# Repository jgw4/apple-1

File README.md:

This repository is a collection of different projects I've found around the internet relating to building a near-exact clone of the Apple-1 computer, as well as the home of the "Doppel-1" replica Apple-1 PCB. My intention is for it to act as a central repository for information that may otherwise be obscure decentralized, or link rot in the future. For aspiring builders, having everything in one place helps with prep work, troubleshooting, and familiarizes with the scope of the project.

For more information on each project, see the README.md within each subdirectory listed below.

## Contents
For further information on the projects in questions, read the README.md within each directory:

[`/mainboard/`](./mainboard/) - Project folder for the Doppel-1

[`/doc/`](./doc/) - Contains various instruction manuals for building, soldering, wiring, and using the Apple-1 and its various accessories

[`/aci/`](./aci/) - Project folder for rebuilding the Apple Cassette Interface in KiCad (Complete)

[`/serialboard/`](./serialboard/) - Project folder for rebuilding the Apple Serial Interface in KiCad

[`/graphicard/`](./graphicard/) - Mirror and minor alteration of the original P-L4B graphics card [here](https://p-l4b.github.io/graphic/) based on the Texas Instruments VDP TMS9918A. It has been modified cosmetically to look more similar to the Apple Cassette Interface. This project is licensed under CC BY 4.0 by the creator.

[`/protoboard/`](./protoboard/) - Mirror and minor alteration of the original P-L4B proto board [here](https://p-l4b.github.io/proto/). It has been modified cosmetically to look more similar to the Apple Cassette Interface. This project is licensed under CC BY 4.0 by the creator.

[`/risercard/`](./risercard/) - Mirror and minor alteration of the original P-L4B riser board [here](https://p-l4b.github.io/riser/). It has been modified cosmetically to look more similar to the Apple Cassette Interface. This project is licensed under CC BY 4.0 by the creator.

[`/datanetics_modern/`](./datanetics_modern/)- Datanetics Keyboard - Modern Version (Built by [@schlae](https://github.com/schlae/replica-datanetics))

[`/datanetics_original`](./datanetics_original/) - Datanetics Keyboard (Original) (Built by [willegal](https://www.willegal.net/appleii/apple1-datanetics.htm))

[`/software/`](./software/) - A repository of Cassette interface software (.wav) files for use with the Apple-1

[`/fw/`](./fw/) - Copies of wozmon.asm and wozaci.asm firmware files

[`/img/`](./img/) - support image files for various projects

## Other Things to check out

[P-Lab Projects](https://p-l4b.github.io) - Hosts various neat expansion cards and mods for the apple-1, such as a Wi-Fi Card, SD Storage card, riser card, sound card, Video card, various IC replacement boards, expansion port breadboards, and much more. Really cool stuff!

[Erik's Ponderings - Building an Apple-1](https://blog.bruchez.name/posts/apple-1-reproduction-part-1-components/) - Erik Bruchez documented his process of building an exceptional Apple-1 clone in great detail, including some great tips for power supply building, adding more decoupling capacitors, mechanical tips, and more. Really neat to check out, especially before you build one of your own

## Goals and Contributing

If you'd like to contribute, I'm always happy to accept work on anything that makes these files more accurate and complete. For more details, see the `readme.md` file located within each board's folder

### Schematics
- Schematic files need creating for the original Datanetics keyboard
### Gerber Files
Gerbers based on the PCB files have not yet been generated. only the original imported gerbers are located within the respective board's folder

## Future Goals
In the future, once the above goals are met and I'm satisfied with them, I may consider working on an altered version of the main board that, while maintaining the same number and nature of the components, makes adequate substitutes such that another curious hobbyist would be able to buy as many components as possible off-the-shelf without having to hunt for "unicorn" parts. I'd also like to address electrical issues found by various hobbyists relating to stability and performance of the board

I'd like the ability to build one to be cheap and available to anyone who wants to do it, without having to sacrifice much at all in the way of board or schematic integrity. I would also like to provide a BOM that includes all required sockets needed for all the DIP chips in the system

## Acknowledgements

This repository contains only a fraction of original work. mostly, it is an amalgamation of a few different projects related to documenting and reproducing the Apple-1 Computer, with my work being mainly relegated to tying the gerber files and schematics together into a cohesive whole KiCad project. The attributions for the various portions of the project files are in the table above
* I am not sure the original source of the Mainboard PCB gerber files. the Applefritter forum post remarks that they were posted on an Apple-1 enthusiasts facebook group, but I do not have facebook nor would i know how to track down the original post. If anyone can give proper attribution to the files please reach out.

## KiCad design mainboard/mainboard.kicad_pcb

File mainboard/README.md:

# About the "Doppel-1"
My personal contributions to this repo is the "Doppel-1", a new Replica PCB that is somewhat unique among clone boards floating around the internet. This is being done by working off of an imported copy of gerber files for the "PCB-11" replica that I found on [Applefritter Forums](https://www.applefritter.com/content/apple-1-replica-gerber-files), which were posted originally on a facebook group. The "PCB-11" is, I believe, the most common replica board you will see pictures of online as this is the only replica (that I know of) where the gerbers have been made publicly available. These are often marked on the back in the bottom right with "Apple 1 replica 2012-2016" in soldermasked copper. If a replica board was purchased post-2020, it is likely that it is based on these gerber files, as the Mimeo-1 has been out of production since that time and up unto the time of writing.

The Doppel-1 can be considered a complete native rebuilding of "PCB-11" in KiCad, whereby the board has its own set of custom footprints that are unique to the apple-1, 3d models, native KiCad filled zones, rule areas, text elements (where possible), traces, and netclasses, as well as error fixes and fabrication notes for a production-ready PCB. Notable mistakes from the original vary from the file itself, to the schematics, to fabrication choices by the customer or the manufacturer. Clarifying remarks have been made to ensure that the PCB is being fabricated to make a reasonable replica. 

## Status of the Doppel-1

* All footprints have been designed, linked, and placed on the board
* All board text is contained within the top board layer. I have decided that there is no font matched well enough at this time to rely on a font alone. Only shapes have been redrawn at the footprint level.
* Need to fix issues with a few improper diode silkscreen arrow placements
* Proper trace widths and clearances still need assigned to all traces, ensuring proper spacing from all solder pads and enforcing a more rigorous Design Rules Check.
* a few remaining schematic parity errors.

## Design Notes And Changes
I have made some remarks about my observations so far:

1) The silkscreen text on the Apple-1 PCB is extremely difficult to reproduce. By all accounts it was hand-stenciled, and I have spent more time than I care to admit comparing uniform-stroke technical typefaces that are meant to replicate leroy lettering or other technical stencil packages that are freely available online, but none of them have quite matched what I have seen on the PCB-11 and on other clones. I have messed around with the font "Routed Gothic" and found it to be closest but kerning is not quite there, and it still does not match with the characters aforementioned. I can hack my way to passable kerning by adjusting the height-width ratio of the text boxes but it is not ideal. I believe Iwater GMaru Gothic Pro is a better match to the original, however that is a paid font that I am unwilling to obtain due to licensing. For any future work on a custom font for this computer, I have included a character "Proof Area" in the PCB file which contains every character on the board.

2) The solder pads on the DIP sockets and breadboard area on "PCB-11" are round on both front and back layers, while on original units, the solderpads were actually different on the back side vs the front. On the back they were a squashed oval (basically an obround but the end arcs share a center point with the rectangle's center point), and on the front they were smaller, tangent obrounds. This was most likely done to make it easy to solder while leaving room for trace paths on the front. This is something a lot of replicas miss.

3) The trace leading to the positive lead between B&C @16 has been adjusted to match the Mimeo-1

4) The trace between C&D @15 leeting to the via below IN914 diode at a 45 degree angle has been moved down slightly to match the Mimeo-1

5) silkscreen outlines for DIP sockets has been increased to a width of 10mils to match what is expected

6) In the original manual's schematics, as well as the ones made by Nicolas, there is an error in the pinouts listed for the TO-220 diodes (REG1,REG3,REG4/LM320 MP-5/LM320 MP-12/LM340 MP-12). LM320 has ground at pin 1, while in and out are pins 2&3, respectively.LM340 has ground at 2 and in/out at 1/3 like a more standard diode in this package. This was discovered by DRC error checking.

7) The top right mounting via has been moved right 100mils to match Mike Willegal's case dimension [here](https://www.willegal.net/appleii/apple1-enclosure.htm). My assumption is that these are truer than what were originally on the board

8) The original applefritter post had a user comment that noted the following issues. My comments are appended to the original marks:
- The original has a matte finish, this one has a sligtly brighter green - This is a fabrication preference/availability, not with the design of the board. see "Manufacturing Notes".
- The silkscreen doesn't cover the plated areas without soldermask.
- The DIP and breadboard solder pads should be wider although it only really matters in the breadboard area. - See point 2 above, much scrutiny went into the shape of the dip pads on this board.
- The video adjustment pot pads are  narrower by 0.025", making it difficult to insert the trimpot. - The 100 Ohm pot has been replaced with a standard footprint that should rectify the issue

## Manufacturing Notes:

If you are going to get your own replica board manufactured, read this first:

1) Normally the green finish provided by PCB manufacturers is way too dark. It has become clear to me that it will be almost impossible to replicate near-exact finishes for small volume with any direct-to-customer fabricators. If the fabricator does allow for lighter green finishes and/or matte green, these colors should be selected instead of a "Standard" green.

2) Boards that are finished with hard gold or using an ENIG process (i.e. full-board gold plating) are unable to also accomodate silkscreening on top of non-soldermasked copper. This is extremely evident in the top-right corner of the board where diode markings are missing where the gold is plated over the copper. It is understandable to desire gold for the longevity of the board, but doing so will produce a poor replica. Gold plating should be confined to the edge fingers only, with the rest done in HAL SnPb.

## Why?

Why did I do this? as Mike Willegal said, If you have to ask that question, this project isn't for you. I have had a strange fascination for the Apple-1 ever since I was a kid. I've been drawn to the technical artistry of the board, the simplicity of it, and find the assembly process and case design around it a very cool method of self-expression.

# Contributing
1) To properly view the pcb file's text elements, please download and install "Routed Gothic" font located in `/doc/`. This is the closest match I have found to the original PCB lettering in font form and is based on the Leroy stenciling system common with draftsman before computer fonts.

2) I have a near certain guess that the original apple-1 pcb was designed using mils. Thus, I would strongly encourage any user working on this board to set their units to mils and not mm. The original PCB-11 file was most likely not made by an American, as there are many metric dimensions scattered throughout the document. However building in nice round mil numbers should be the standard for this project

3) please submit a pull request listing in detail all changes you have made or would like to make, preferably with pictures. This can help avoid any duplicate work

4) Issues can also be raised, which I also enthusiastically accept. If you spot issues with the design of the board, please post an issue to the repository.

5) I am looking also for some more specific input on trace clearance. Since resizing the dip solderpads, clearance has been the biggest DRC issue. I would like to know what spacing was used on the original board so I can preserve that. Current clearance is set at 5 mils.

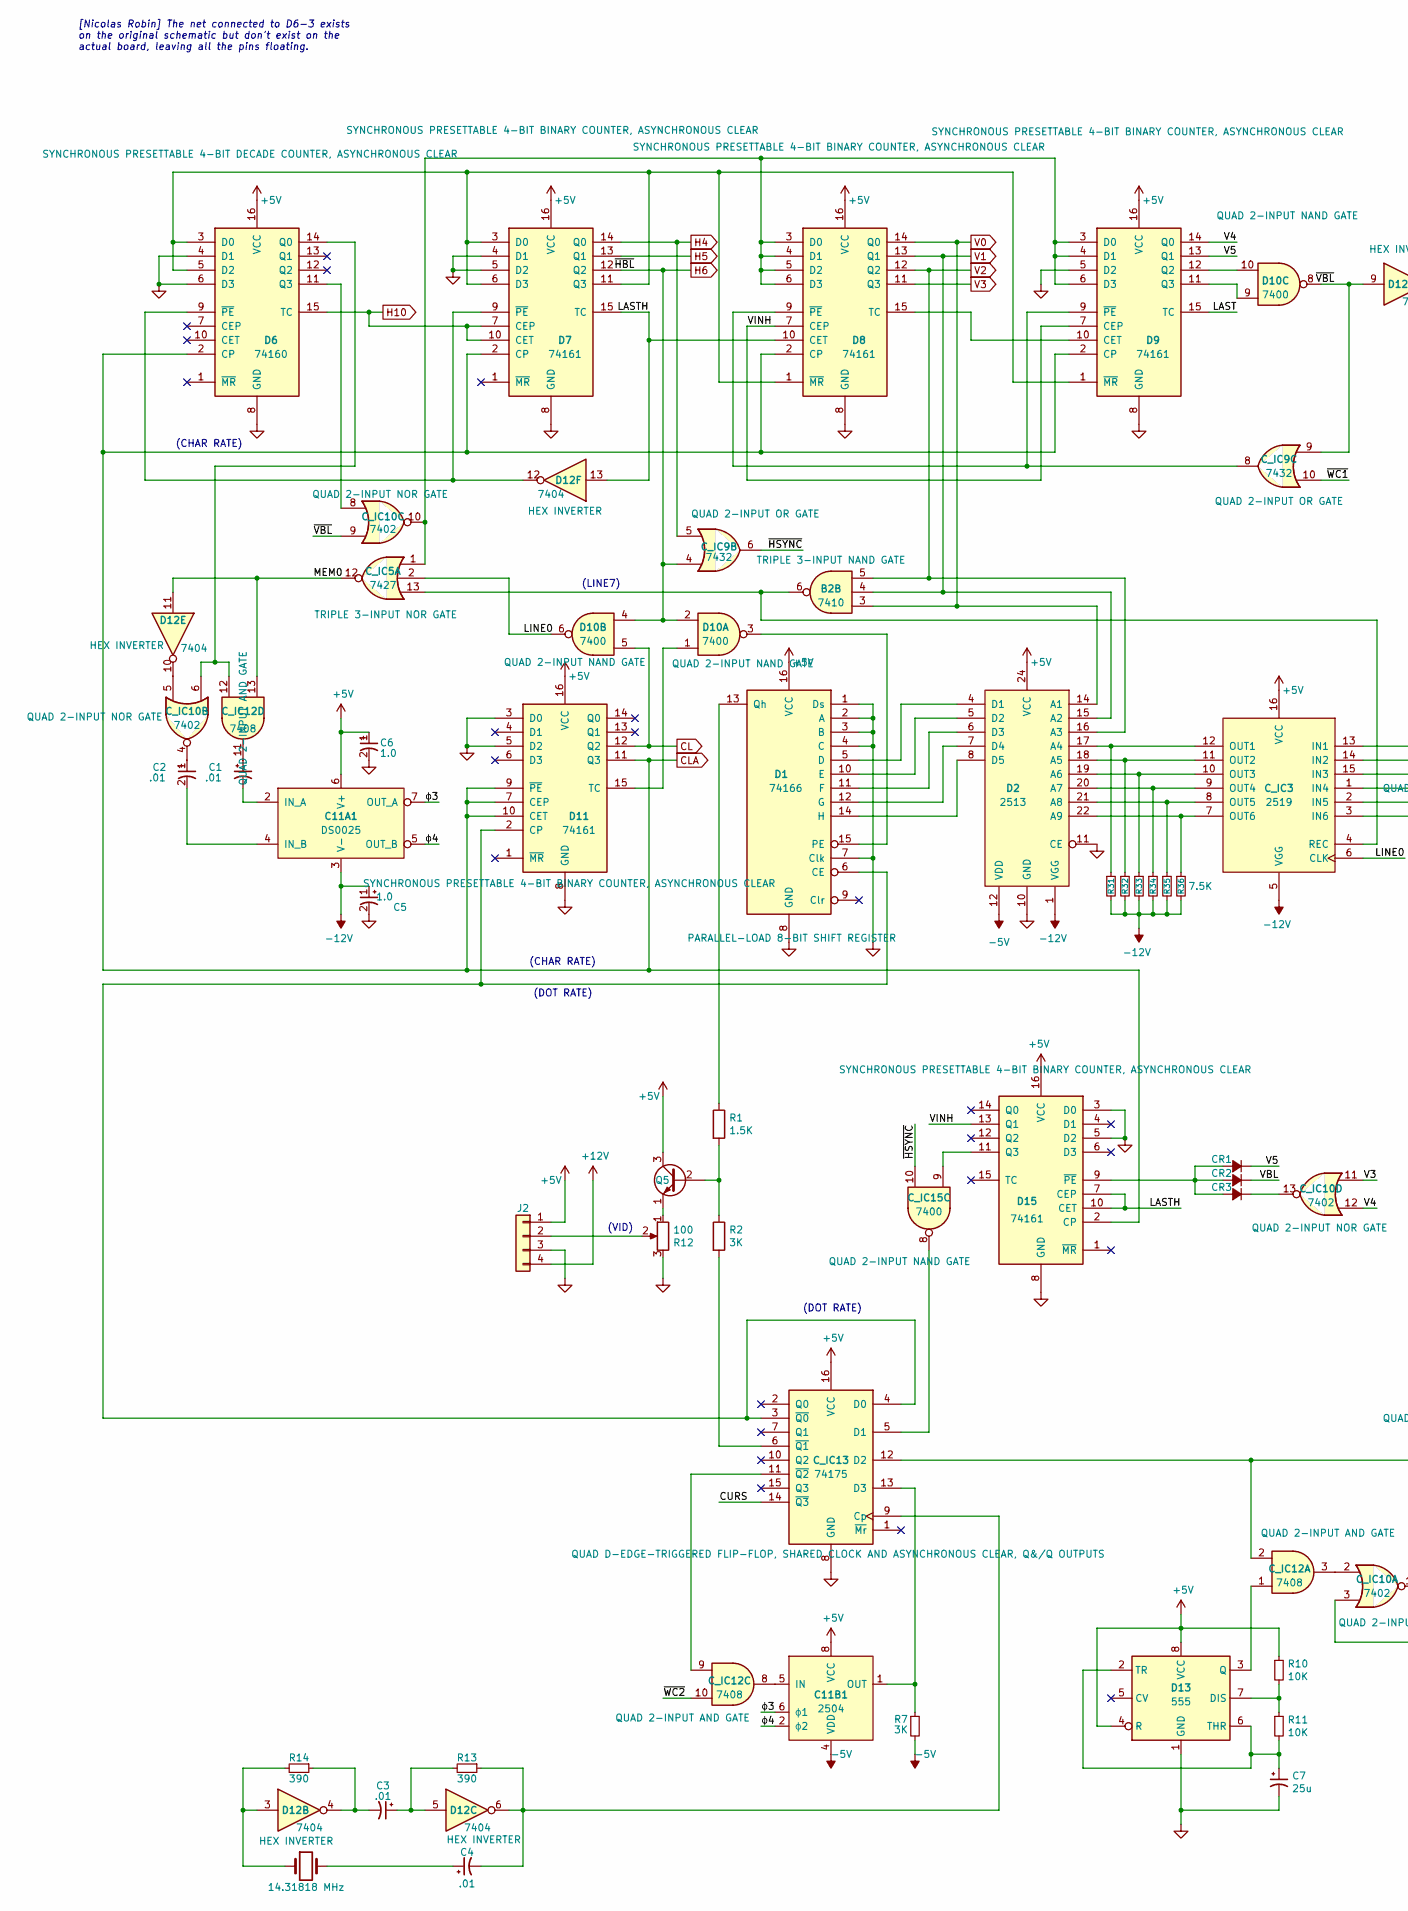
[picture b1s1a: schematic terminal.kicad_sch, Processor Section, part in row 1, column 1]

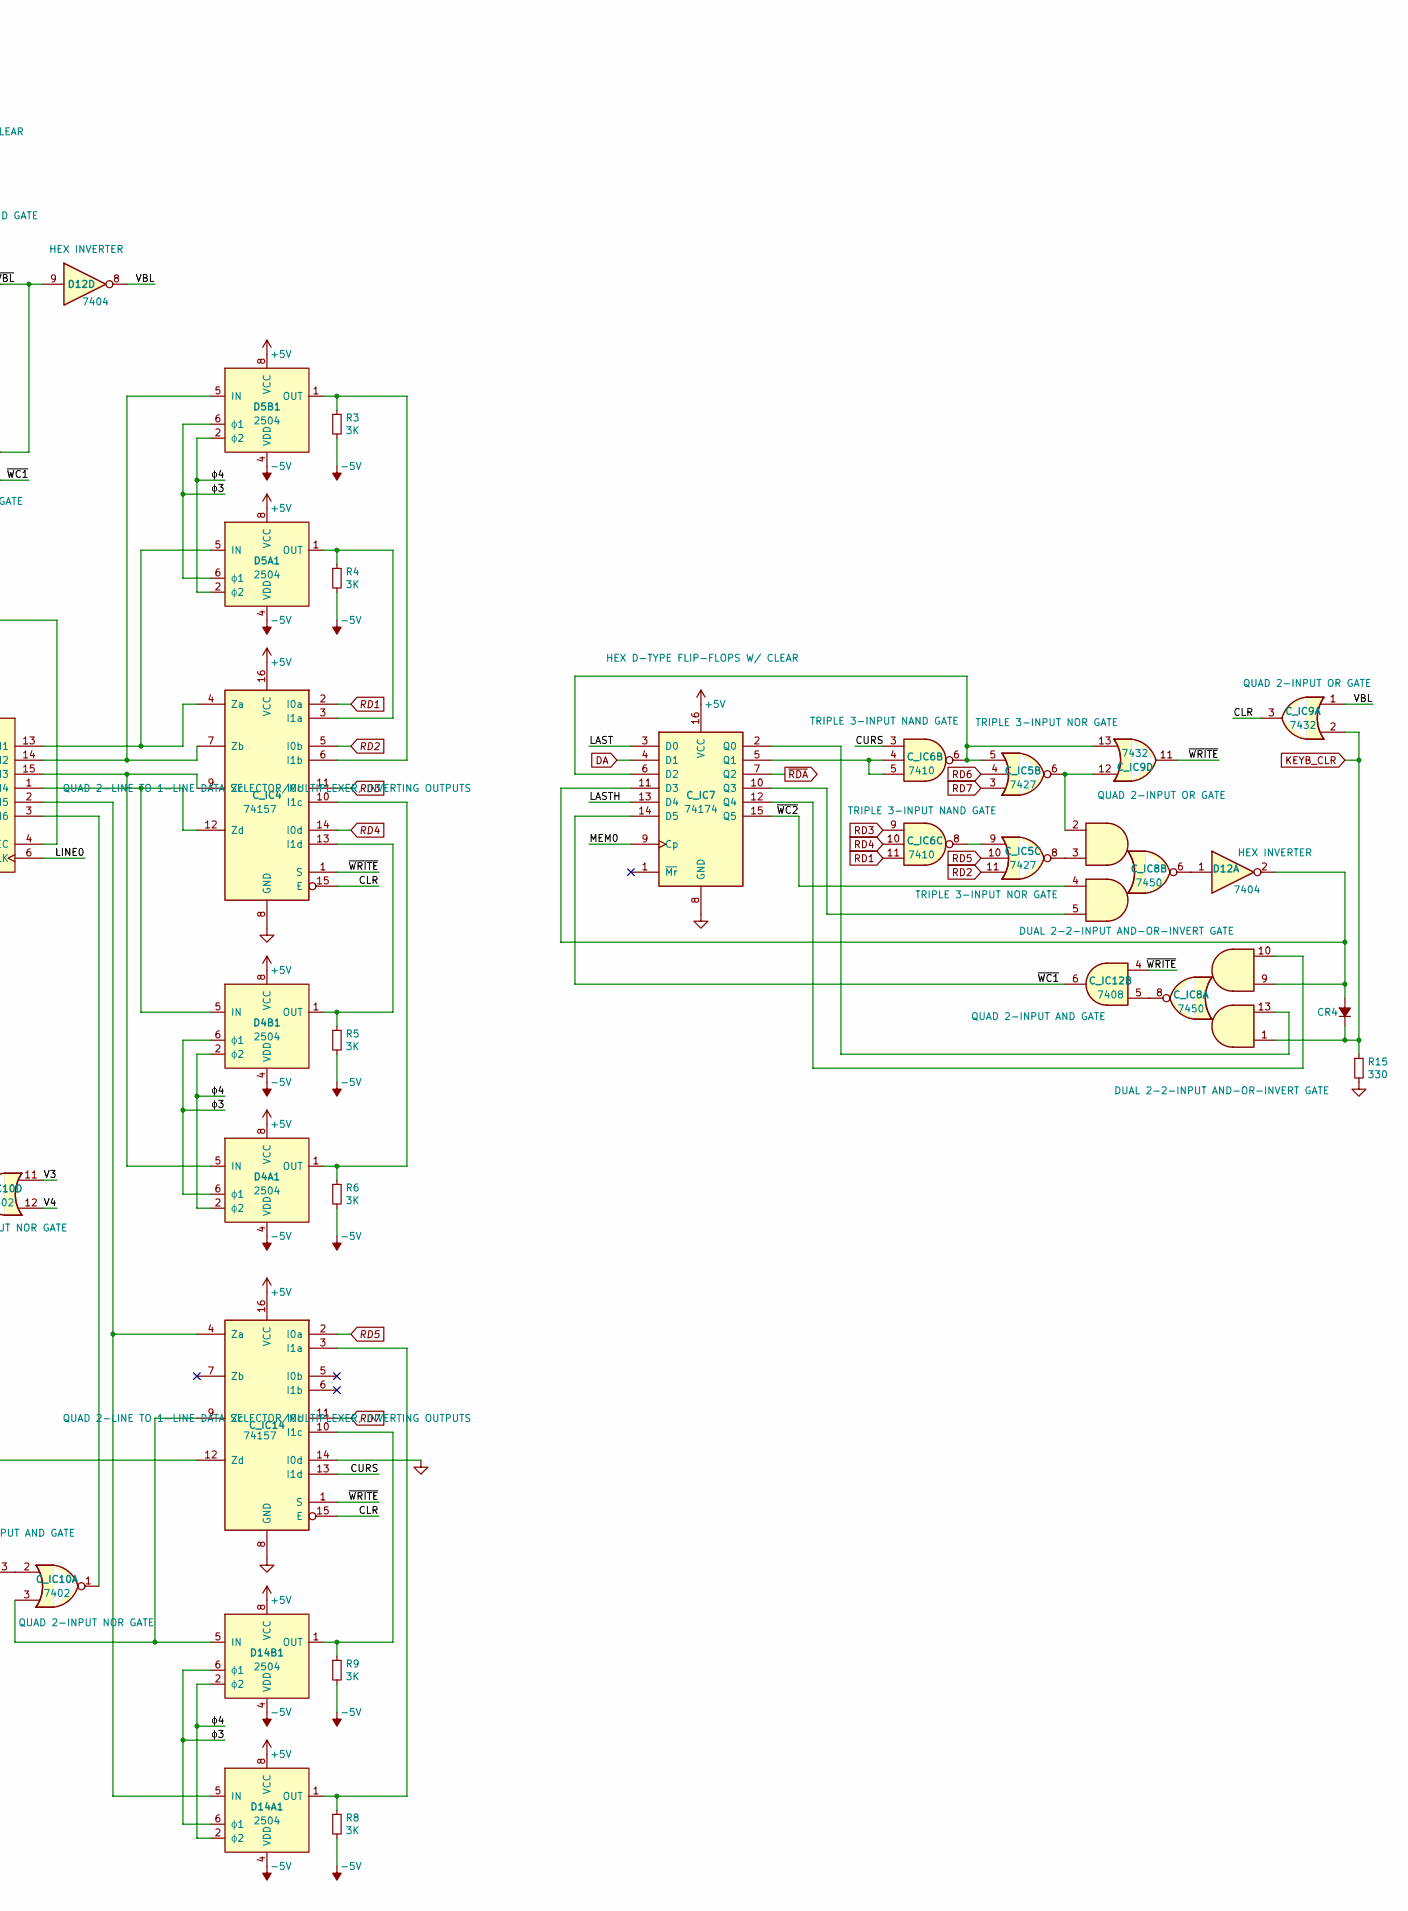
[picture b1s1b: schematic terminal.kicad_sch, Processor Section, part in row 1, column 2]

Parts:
B2: 7410; apple-1_DIP-14_W7.62mm
C1, C2, C3, C4: .01; apple-1_C_Disc_D16.0mm_W5.0mm_P7.50mm
C5, C6: 1.0; apple-1_C_Disc_D16.0mm_W5.0mm_P7.50mm
C7: 25u; CP_Axial_25u
C11A1: DS0025; apple-1_DIP-8_W7.62mm
C11B1: 2504; apple-1_DIP-8_W7.62mm
CR1, CR2, CR3, CR4: 1N914; apple-1_D_DO-35_SOD27_P10.16mm_Horizontal_altarrow
C_IC3: 2519; apple-1_DIP-16_W7.62mm
C_IC4, C_IC14: 74157; apple-1_DIP-16_W7.62mm
C_IC5: 7427; apple-1_DIP-14_W7.62mm
C_IC6: 7410; apple-1_DIP-14_W7.62mm
C_IC7: 74174; apple-1_DIP-16_W7.62mm
C_IC8: 7450; apple-1_DIP-14_W7.62mm
C_IC9: 7432; apple-1_DIP-14_W7.62mm
C_IC10: 7402; apple-1_DIP-14_W7.62mm
C_IC12: 7408; apple-1_DIP-14_W7.62mm
C_IC13: 74175; apple-1_DIP-16_W7.62mm
C_IC15: 7400; apple-1_DIP-14_W7.62mm
D1: 74166; apple-1_DIP-16_W7.62mm
D2: 2513; apple-1_DIP-24_18.0mmx34.29mm_W15.24mm
D4A1, D4B1, D5A1, D5B1, D14A1, D14B1: 2504; apple-1_DIP-8_W7.62mm
D6: 74160; apple-1_DIP-16_W7.62mm
D7, D8, D9, D11, D15: 74161; apple-1_DIP-16_W7.62mm
D10: 7400; apple-1_DIP-14_W7.62mm
D12: 7404; apple-1_DIP-14_W7.62mm
D13: 555; apple-1_DIP-8_W7.62mm
J2: Conn_01x04; apple-1_JST_VH_B4P-VH_1x04_P3.96mm_Vertical
Q5: MPS3704; apple-1_TO-92_HandSolder
R1: 1.5K; apple-1_R_Axial_DIN0207_L6.3mm_D2.5mm_P10.16mm_Horizontal
R2, R3, R4, R5, R6, R7, R8, R9: 3K; apple-1_R_Axial_DIN0207_L6.3mm_D2.5mm_P10.16mm_Horizontal
R10, R11: 10K; apple-1_R_Axial_DIN0207_L6.3mm_D2.5mm_P10.16mm_Horizontal
R12: 100; apple-1_Potentiometer_Bourns_3329H_Vertical
R13, R14: 390; apple-1_R_Axial_DIN0207_L6.3mm_D2.5mm_P10.16mm_Horizontal
R15: 330; apple-1_R_Axial_DIN0207_L6.3mm_D2.5mm_P10.16mm_Horizontal
R31, R32, R33, R34, R35, R36: 7.5K; apple-1_R_Axial_DIN0207_L6.3mm_D2.5mm_P10.16mm_Horizontal
Y1: 14.31818 MHz; apple-1_Crystal_HC49-U_Vertical

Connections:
+5V: C6.1, C11A1.6 (V+), C11B1.8 (VCC), C_IC3.16 (VCC), C_IC4.16 (VCC), C_IC7.16 (VCC), C_IC13.16 (VCC), C_IC14.16 (VCC), D1.16 (VCC), D2.24 (VCC), D4A1.8 (VCC), D4B1.8 (VCC), D5A1.8 (VCC), D5B1.8 (VCC), D6.16 (VCC), D7.16 (VCC), D8.16 (VCC), D9.16 (VCC), D11.16 (VCC), D13.4 (R), D13.8 (VCC), D14A1.8 (VCC), D14B1.8 (VCC), D15.16 (VCC), J2.1, Q5.3 (C), R10.1; also elsewhere on the board
+12V: J2.4; also elsewhere on the board
-5V: C11B1.4 (VDD), D2.12 (VDD), D4A1.4 (VDD), D4B1.4 (VDD), D5A1.4 (VDD), D5B1.4 (VDD), D14A1.4 (VDD), D14B1.4 (VDD), R3.2, R4.2, R5.2, R6.2, R7.2, R8.2, R9.2; also elsewhere on the board
-12V: C5.1, C11A1.3 (V-), C_IC3.5 (VGG), D2.1 (VGG), R31.2, R32.2, R33.2, R34.2, R35.2, R36.2; also elsewhere on the board
/Terminal Section/CLR: C_IC4.15 (E), C_IC9.3, C_IC14.15 (E)
/Terminal Section/CURS: C_IC6.3, C_IC13.14 (~Q3), C_IC14.13 (I1d)
/Terminal Section/LAST: C_IC7.3 (D0), D9.15 (TC)
/Terminal Section/LASTH: C_IC7.13 (D4), D7.15 (TC), D8.10 (CET), D12.13, D15.7 (CEP), D15.10 (CET)
/Terminal Section/LINE0: C_IC3.6 (CLK), C_IC5.2, D10.6
/Terminal Section/MEM0: C_IC5.12, C_IC7.9 (Cp), C_IC12.13, D12.11
/Terminal Section/V4: C_IC10.12, D9.14 (Q0)
/Terminal Section/V5: CR1.1 (K), D9.13 (Q1)
/Terminal Section/VBL: CR2.1 (K), C_IC9.1, D12.8
/Terminal Section/VINH: D8.7 (CEP), D9.7 (CEP), D15.13 (Q1)
/Terminal Section/~HSYNC: C_IC9.6, C_IC15.10
/Terminal Section/~VBL: C_IC9.9, C_IC10.9, D10.8, D12.9
/Terminal Section/~WC1: C_IC7.14 (D5), C_IC9.10, C_IC12.6
/Terminal Section/~WC2: C_IC7.15 (Q5), C_IC8.4, C_IC12.10
/Terminal Section/~WRITE: C_IC4.1 (S), C_IC9.11, C_IC12.4, C_IC14.1 (S)
/Terminal Section/ɸ3: C11A1.7 (OUT_A), C11B1.6 (ɸ1), D4A1.6 (ɸ1), D4B1.6 (ɸ1), D5A1.6 (ɸ1), D5B1.6 (ɸ1), D14A1.6 (ɸ1), D14B1.6 (ɸ1)
/Terminal Section/ɸ4: C11A1.5 (OUT_B), C11B1.2 (ɸ2), D4A1.2 (ɸ2), D4B1.2 (ɸ2), D5A1.2 (ɸ2), D5B1.2 (ɸ2), D14A1.2 (ɸ2), D14B1.2 (ɸ2)
CL: D10.5, D11.12 (Q2); also elsewhere on the board
CLA: D6.2 (CP), D7.2 (CP), D8.2 (CP), D9.2 (CP), D11.7 (CEP), D11.9 (~PE), D11.10 (CET), D11.11 (Q3), D15.2 (CP); also elsewhere on the board
DA: C_IC7.4 (D1); also elsewhere on the board
H4: C_IC9.5, D7.14 (Q0); also elsewhere on the board
H5: D7.13 (Q1); also elsewhere on the board
H6: C_IC9.4, D7.12 (Q2), D10.2, D10.4; also elsewhere on the board
H10: D6.15 (TC), D7.7 (CEP), D7.10 (CET); also elsewhere on the board
KEYB_CLR: CR4.1 (K), C_IC8.1, C_IC9.2, R15.1; also elsewhere on the board
unnamed: C1.1, C_IC12.11
unnamed: C2.1, C_IC10.4
unnamed: C3.1, D12.5, R13.2
unnamed: C3.2, D12.4, R14.1
unnamed: C4.1, Y1.2
unnamed: C1.2, C11A1.2 (IN_A)
unnamed: C2.2, C11A1.4 (IN_B)
unnamed: C11B1.5 (IN), C_IC12.8
unnamed: C11B1.1 (OUT), C_IC13.13 (D3), R7.1
unnamed: CR1.2 (A), CR2.2 (A), CR3.2 (A), D15.9 (~PE)
unnamed: CR3.1 (K), C_IC10.13
unnamed: CR4.2 (A), C_IC7.11 (D3), C_IC8.9, D12.2
unnamed: C_IC3.13 (IN1), C_IC4.4 (Za), D5A1.5 (IN)
unnamed: C_IC3.14 (IN2), C_IC4.7 (Zb), D5B1.5 (IN)
unnamed: C_IC3.15 (IN3), C_IC4.9 (Zc), D4A1.5 (IN)
unnamed: C_IC3.1 (IN4), C_IC4.12 (Zd), D4B1.5 (IN)
unnamed: C_IC3.3 (IN6), C_IC10.1
unnamed: C_IC3.12 (OUT1), D2.17 (A4), R31.1
unnamed: C_IC3.11 (OUT2), D2.18 (A5), R32.1
unnamed: C_IC3.10 (OUT3), D2.19 (A6), R33.1
unnamed: C_IC3.9 (OUT4), D2.20 (A7), R34.1
unnamed: C_IC3.8 (OUT5), D2.21 (A8), R35.1
unnamed: C_IC3.7 (OUT6), D2.22 (A9), R36.1
unnamed: B2.6, C_IC3.4 (REC), C_IC5.13
unnamed: C_IC4.3 (I1a), D5A1.1 (OUT), R4.1
unnamed: C_IC4.6 (I1b), D5B1.1 (OUT), R3.1
unnamed: C_IC4.10 (I1c), D4A1.1 (OUT), R6.1
unnamed: C_IC4.13 (I1d), D4B1.1 (OUT), R5.1
unnamed: C_IC5.6, C_IC8.2, C_IC9.12
unnamed: C_IC5.8, C_IC8.3
unnamed: C_IC5.9, C_IC6.8
unnamed: C_IC5.5, C_IC6.6, C_IC7.6 (D2), C_IC9.13
unnamed: C_IC7.2 (Q0), C_IC8.13
unnamed: C_IC6.4, C_IC6.5, C_IC7.5 (Q1)
unnamed: C_IC7.10 (Q3), C_IC8.5
unnamed: C_IC7.12 (Q4), C_IC8.10
unnamed: C_IC8.6, D12.1
unnamed: C_IC10.2, C_IC12.3
unnamed: C_IC10.5, D12.10
unnamed: C_IC8.8, C_IC12.5
unnamed: C4.2, C_IC13.9 (Cp), D12.6, R13.1
unnamed: C_IC13.3 (~Q0), C_IC13.4 (D0), D1.6 (CE), D11.2 (CP)
unnamed: C_IC13.5 (D1), C_IC15.8
unnamed: C_IC12.2, C_IC13.12 (D2), C_IC14.12 (Zd)
unnamed: C_IC13.6 (~Q1), R2.2
unnamed: C_IC12.9, C_IC13.11 (~Q2)
unnamed: C_IC14.3 (I1a), D14A1.1 (OUT), R8.1
unnamed: C_IC14.10 (I1c), D14B1.1 (OUT), R9.1
unnamed: C_IC3.2 (IN5), C_IC14.4 (Za), D14A1.5 (IN)
unnamed: C_IC10.3, C_IC14.9 (Zc), D14B1.5 (IN)
unnamed: D1.5 (D), D2.4 (D1)
unnamed: D1.10 (E), D2.5 (D2)
unnamed: D1.11 (F), D2.6 (D3)
unnamed: D1.12 (G), D2.7 (D4)
unnamed: D1.14 (H), D2.8 (D5)
unnamed: D1.15 (PE), D10.3
unnamed: D1.13 (Qh), R1.1
unnamed: D6.3 (D0), D6.5 (D2), D7.3 (D0), D7.6 (D3), D7.11 (Q3), D8.1 (~MR), D9.1 (~MR)
unnamed: C_IC10.6, C_IC12.12, D6.14 (Q0)
unnamed: C_IC10.8, D6.11 (Q3)
unnamed: D6.9 (~PE), D7.9 (~PE), D12.12
unnamed: C_IC5.1, C_IC10.10, D8.3 (D0), D8.4 (D1), D8.5 (D2), D8.6 (D3), D9.3 (D0), D9.4 (D1), D9.6 (D3)
unnamed: D8.15 (TC), D9.10 (CET)
unnamed: C_IC9.8, D8.9 (~PE), D9.9 (~PE)
unnamed: D9.12 (Q2), D10.10
unnamed: D9.11 (Q3), D10.9
unnamed: D10.1, D11.15 (TC)
unnamed: D12.3, R14.2, Y1.1
unnamed: D13.7 (DIS), R10.2, R11.1
unnamed: C_IC12.1, D13.3 (Q)
unnamed: C7.1, D13.2 (TR), D13.6 (THR), R11.2
unnamed: C_IC15.9, D15.11 (Q3)
unnamed: J2.2, R12.2
unnamed: Q5.2 (B), R1.2, R2.1
unnamed: Q5.1 (E), R12.1
RD1: C_IC4.2 (I0a), C_IC6.11; also elsewhere on the board
RD2: C_IC4.5 (I0b), C_IC5.11; also elsewhere on the board
RD3: C_IC4.11 (I0c), C_IC6.9; also elsewhere on the board
RD4: C_IC4.14 (I0d), C_IC6.10; also elsewhere on the board
RD5: C_IC5.10, C_IC14.2 (I0a); also elsewhere on the board
RD6: C_IC5.4; also elsewhere on the board
RD7: C_IC5.3, C_IC14.11 (I0c); also elsewhere on the board
V0: B2.3, D2.14 (A1), D8.14 (Q0); also elsewhere on the board
V1: B2.4, D2.15 (A2), D8.13 (Q1); also elsewhere on the board
V2: B2.5, D2.16 (A3), D8.12 (Q2); also elsewhere on the board
V3: C_IC10.11, D8.11 (Q3); also elsewhere on the board
~RDA: C_IC7.7 (Q2); also elsewhere on the board

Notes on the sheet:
(LINE7)
(CHAR RATE)
[Nicolas Robin] The net connected to D6-3 exists on the original schematic but don't exist on the actual board, leaving all the pins floating.
(DOT RATE)
(VID)

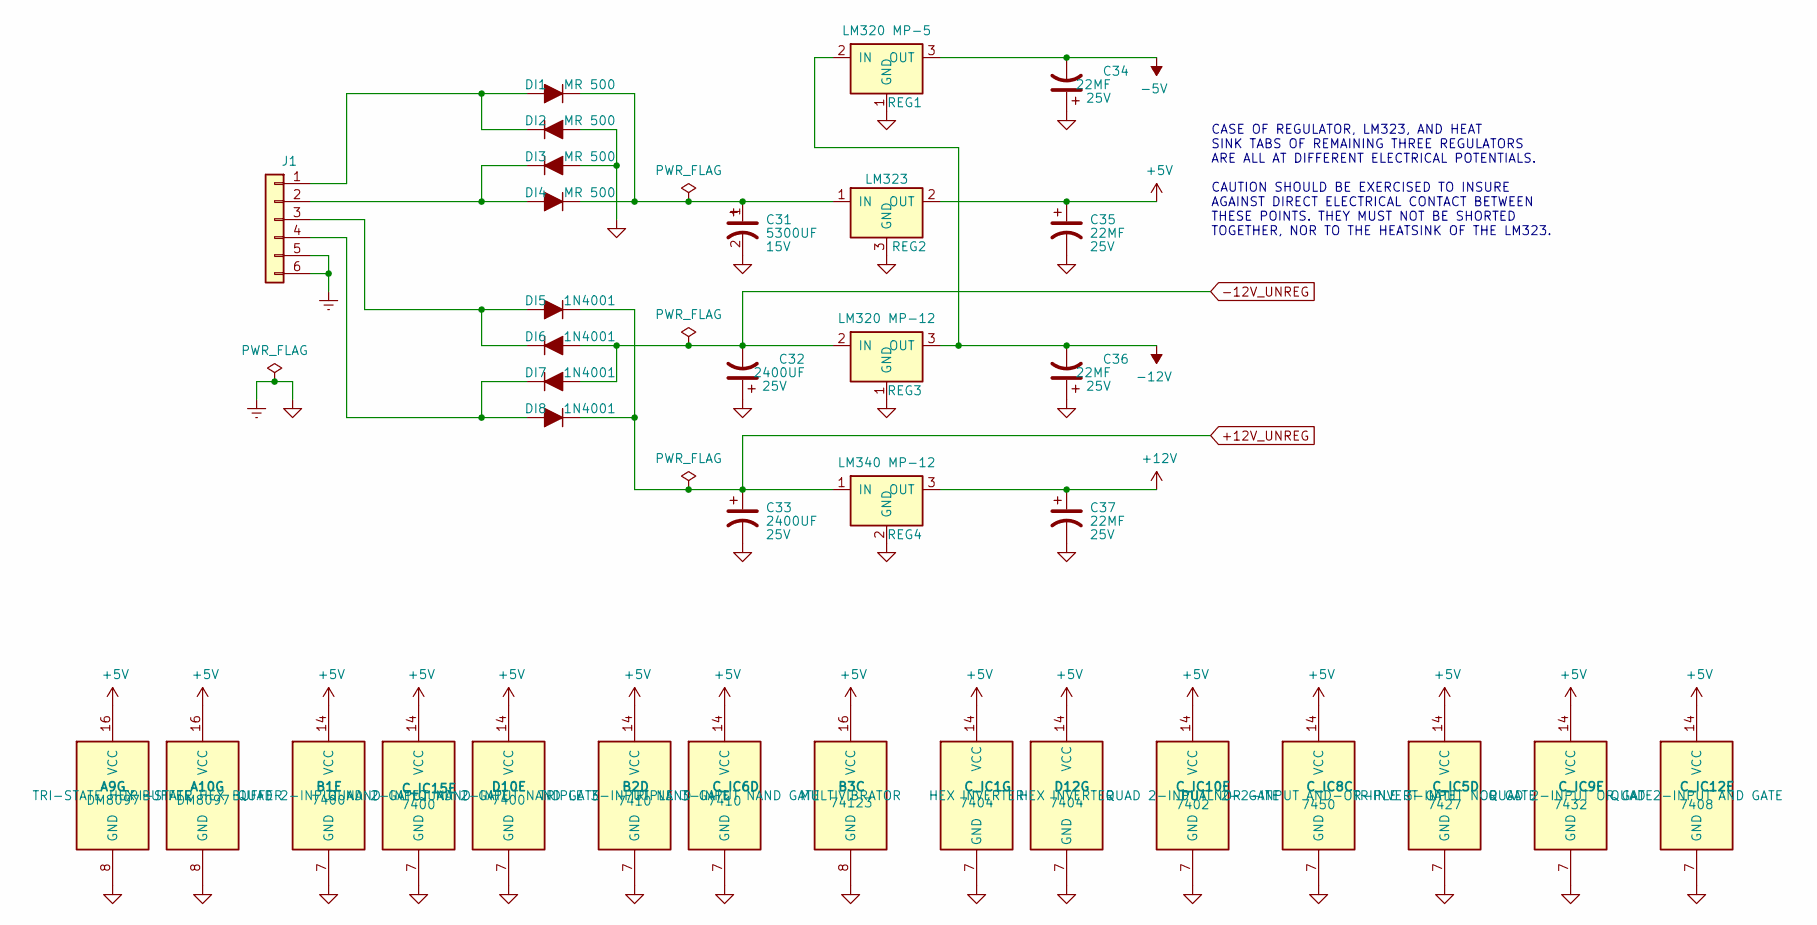
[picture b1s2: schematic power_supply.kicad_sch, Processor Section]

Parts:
A9, A10: DM8097; apple-1_DIP-16_W7.62mm
B1: 7400; apple-1_DIP-14_W7.62mm
B2: 7410; apple-1_DIP-14_W7.62mm
B3: 74123; apple-1_DIP-16_W7.62mm
C31: 5300UF; CP_Axial_5300uF; Voltage 15V
C32, C33: 2400UF; apple-1_CP_2400UF_25V_-+; Voltage 25V
C34, C36, C37: 22MF; apple-1_C_Axial_L12.0mm_D6.5mm_P20.00mm_Horizontal; Voltage 25V
C35: 22MF; apple-1_C_Axial_22MF_25V_P1200mils_Horizontal; Voltage 25V
C_IC1: 7404; apple-1_DIP-14_W7.62mm
C_IC5: 7427; apple-1_DIP-14_W7.62mm
C_IC6: 7410; apple-1_DIP-14_W7.62mm
C_IC8: 7450; apple-1_DIP-14_W7.62mm
C_IC9: 7432; apple-1_DIP-14_W7.62mm
C_IC10: 7402; apple-1_DIP-14_W7.62mm
C_IC12: 7408; apple-1_DIP-14_W7.62mm
C_IC15: 7400; apple-1_DIP-14_W7.62mm
D10: 7400; apple-1_DIP-14_W7.62mm
D12: 7404; apple-1_DIP-14_W7.62mm
DI1, DI2, DI3, DI4: MR 500; apple-1_D_5W_P10.16mm_Horizontal
DI5, DI6, DI7, DI8: 1N4001; apple-1_D_5W_P10.16mm_Horizontal
J1: Conn_01x06; apple-1_JST_VH_B6P-VH_1x06_P3.96mm_Vertical
REG1: LM320 MP-5; LM320 MP-5 (TO-220-3_Vertical_SpacedPins)
REG2: LM323; TO-3
REG3: LM320 MP-12; LM320 MP-12 (TO-220-3_Vertical_SpacedPins)
REG4: LM340 MP-12; LM340-12 (TO-220-3_Vertical_SpacedPins)

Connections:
+5V: A9.16 (VCC), A10.16 (VCC), B1.14 (VCC), B2.14 (VCC), B3.16 (VCC), C35.1, C_IC1.14 (VCC), C_IC5.14 (VCC), C_IC6.14 (VCC), C_IC8.14 (VCC), C_IC9.14 (VCC), C_IC10.14 (VCC), C_IC12.14 (VCC), C_IC15.14 (VCC), D10.14 (VCC), D12.14 (VCC), REG2.2 (OUT); also elsewhere on the board
+12V: C37.1, REG4.3 (OUT); also elsewhere on the board
+12V_UNREG: C33.1, DI5.1 (K), DI8.1 (K), REG4.1 (IN); also elsewhere on the board
-5V: C34.2, REG1.3 (OUT); also elsewhere on the board
-12V: C36.2, REG1.2 (IN), REG3.3 (OUT); also elsewhere on the board
-12V_UNREG: C32.2, DI6.2 (A), DI7.2 (A), REG3.2 (IN); also elsewhere on the board
unnamed 217: DI1.2 (A), DI2.1 (K), J1.1; also elsewhere on the board
unnamed: C31.1, DI1.1 (K), DI4.1 (K), REG2.1 (IN)
unnamed 219: DI3.1 (K), DI4.2 (A), J1.2; also elsewhere on the board
unnamed 220: DI5.2 (A), DI6.1 (K), J1.3; also elsewhere on the board
unnamed 221: DI7.1 (K), DI8.2 (A), J1.4; also elsewhere on the board

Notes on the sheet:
CASE OF REGULATOR, LM323, AND HEAT SINK TABS OF REMAINING THREE REGULATORS ARE ALL AT DIFFERENT ELECTRICAL POTENTIALS. CAUTION SHOULD BE EXERCISED TO INSURE AGAINST DIRECT ELECTRICAL CONTACT BETWEEN THESE POINTS. THEY MUST NOT BE SHORTED TOGETHER, NOR TO THE HEATSINK OF THE LM323.

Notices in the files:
datanetics_modern/datanetics_modern.kicad_pcb:
Copyright (C) 2022 Tube Time
